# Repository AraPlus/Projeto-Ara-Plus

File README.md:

# Projeto-Ara-Plus
Repositório de projeto de um AMBU automatizado desenvolvido por estudantes, pesquisadores e professores da Universidade Federal do ABC (UFABC) para substituir um ventilador pulmonar de forma emergencial nos casos de COVID-19. Este é um trabalho em desenvolvimento, e ainda não está apto para casos clínicos. Futuras atualizações devem ser lançadas em breve.

## Origem do Nome
O nome "Ara" vem do Tupi-Guarani e significa "ar". Portanto o nome Ara-Plus reune uma palava genuinamente brasileira com uma palavra do inglês reconhecida em todo o mundo, significando literalmente "mais ar".

## Descrição geral do sistema

### Requisitos

Conforme destacado pela AMIB – [Associação de Medicina Intensiva Brasileira]() – em sua nota técnica ["Nota técnica sobre características de aparelhos ventiladores artificiais no suporte ao paciente com COVID-19"](http://www.amib.org.br/fileadmin/user_upload/amib/2020/abril/26/Nota_te__cnica_sobre_caracteri__sticas_de_aparelhos_ventiladores_artificiais_no_suporte_ao_paciente_com_COVID-19.pdf) de 26 de abril de 2020 e que atualmente (29/05/2020) subsidia o [PROJETO DE LEI N° 2294, DE 2020, em tramitação no senado,](https://www25.senado.leg.br/web/atividade/materias/-/materia/142132): "No atual cenário de pandemia por COVID-19, diante de uma situação de exceção decorrente do grande número de pacientes com necessidade de ventilação mecânica, listamos abaixo as especificações MÍNIMAS que um ventilador mecânico deve apresentar para ventilar pacientes com COVID-19, em qualquer unidade (pronto socorro, UTI ou outras unidades). Essas características devem estar presentes, independentemente de o equipamento ser ventilador de transporte ou não, ser novo ou reformado:
1. MODOS VCV e/ou PCV;
2. CONTROLE DE DELTA DE PRESSÃO (SOBRE A PEEP) NO MODO PCV (DE 5 A 30 cmH2O) E CONTROLE DE VOLUME CORRENTE INSPIRADO NO MODO VCV (de 50 A 700 ML);
3. CONTROLE DE FiO2 (21 a 100%);
4. PEEP (0 ATE 20 cm H2O);
5. CONTROLE DE TEMPO INSPIRATÓRIO (NO MODO PCV) EM SEGUNDOS (0,3 - 2,0 S) E FLUXO INSPIRATÓRIO (NO MODO VCV) - ATÉ 70L/MIN;
6. CONTROLE DE FREQUÊNCIA RESPIRATÓRIA - 8 a 40 RPM;
7. MEDIDA DE PRESSÃO DE VIAS AÉREAS (MANÔMETRO ANALÓGICO OU DIGITAL);
8. MEDIDA DE VOLUME CORRENTE EXPIRADO SEMPRE QUE POSSÍVEL;
9. ALARME DE PRESSÃO MÁXIMA EM VIAS ÁEREAS, VAZAMENTO E QUEDA DE REDE DE GASES;
10. POSSIBILIDADE DE ANEXAR FILTRO TIPO HEPA DE ALTA CAPACIDADE (N99 OU N100) NO RAMO EXPIRATÓRIO;
11. SE POSSÍVEL, POSSUIR BATERIA COM PELO MENOS 2 HORAS DE CAPACIDADE."

## Lista de Material
Descrição de todas os materiais e peças usados no Ara Plus separados por categorias:

### Partes Eletrônicas

**Diagrama elétrico do acionamento**

**Lista de materiais do acionamento**
 | Referência | Quantidade | Especificação | 
 | --------------- | --------------- | --------------- | 
 | A1 | 1 | Arduino Nano v3.x | 
 | BT1, BT2 | 2 | Bateria 12V/ 7Ah | 
 | BZ1 | 1 | Buzzer ativo 5V | 
 | C1, C4, C5 | 3 | Capacitor 0.33uF | 
 | C2, C6 | 2 | Capacitor 0.1uF | 
 | C3, C7 | 2 | Capacitor 220u
 | D1, D2, D3, D4, D5, D6, D7 | 7 | Diodo 1N4007 | 
 | M1 | 1 | Motor DC | 
 | Q1 | 1 | Transistor BC337 | 
 | RV1 | 1 | Trimpot 10K | 
 | RV2 | 1 | Potenciômetro 10K | 
 | R1, R2, R3, R4, R5, R6, R7 | 7 | Resistor 1K | 
 | S1, S2 | 2 | Sensor Indutivo NPN 12mm | 
 | SW1, SW2 | 2 | Acionador Push Buttom | 
 | U1 | 1 | Display alfanumérico 4 x 20 NHD-0420H1Z | 
 | U2, U3, U4 | 3 | Optoacoplador PC817 | 
 | U5 | 1 | Módulo Ponte H - L298N | 
 | U6, U7 | 2 | Regulador L7805 | 
 | U8 | 1 | Regulador L7812 | 
 | +24V | 1 | Fonte 24V - 5A |

### Partes Mecânicas

## Desenhos de Fabricação / Arquivos de CAD
As informações sobre os desenhos de fabricação das partes mecânicas do AraPlus encontram-se [aqui](desenhos/DESENHOS.md)

### Partes médicas

Propostas em estudo do circuito pneumático:

**Tipo 1 - Com válvula VUP**

**Tipo 2 - Com Diverter e a válvula VAP tampada de um lado**

**Tipo 3 - Com a hipótese do *Diverter* para encaixe na VAP**

## Fotos

Acionamento Mecânico

 ## Descrição dos Testes Funcionais de Bancada (in vitro)
 
**1) Levantamento da Relação PEEP x Pressão Expiratória Máxima (Vál. VAP) x Freq. Respiratória x Volume Inspirado**

**2) Levantamento da freqüência de operação, e relações Ti:Te possíveis**

Avaliar desempenho dinâmico do motor e capacidade de controle de velocidade para ajuste dos tempos.

**3) Levantamento da Relação de FIO2 e Fluxo de Oxigênio (Fluxímetro de parede)**

Referência:
GODOY, Armando Carlos Franco de; VIEIRA, Ronan José. Comparação da FiO2 fornecida por sete modelos de sistema balão-máscara auto-inflável. Rev. Bras. Anestesiol.,  Campinas ,  v. 59, n. 1, p. 21-27,  Feb.  2009 .   Available from <[http://www.scielo.br/scielo.php?script=sci_arttext&pid=S0034-70942009000100004&lng=en&nrm=iso]>. access on  22  June  2020.  [https://doi.org/10.1590/S0034-70942009000100004].

**4) Levantamento da relação de tempos determinadas mecanicamente e pelas curvas de pressão pneumática**

Averiguar para diversas condições se os tempos Ti e Te medidos pelos sensores posicionados no eixo do motor corresponde aos tempos de Ti e Te medidos pela curva de pressão/ fluxo pneumático.

**5) Calibração Estática do Sensor de Pressão**

Levantar curva de pressão medida pelo sensor MPS20N0040d comparando com uma medição de pressão estática (com manômetro U ou manômetro analógico)

**6) Calibração Dinâmica (valores simulados)**

Comparação das curvas de pressão e volume obtidas com um sensor de reverência (Analisador de Gases Fluke VT650) com as curvas de pressão obtidas com o simulador https://girardi.blumenau.ufsc.br/sdvm/, para os mesmos parâmetros ventilatórios.

**7) Calibração Dinâmica (valores experimentais)**

Comparação das curvas de pressão com um sensor de reverência, com as curvas de pressão efetivamente medidas com o sensor MPS20N0040d. Obs: o analisador  Fluke aparentemente só exporta com uma frequência de amostragem máxima de 1Hz, o que não dá uma boa resolução das curvas. A solução seria usar o sensor Magnamed Ventmeter que tem interface RS232.

**8) Determinação do procedimento de calibração do sensor de pressão embarcado**

Estabelecer rotina de calibração do sensor de pressão. Procedimento de manutenção.

## Cronologia do Desenvolvimento
Data dos principais marcos do desenvolvimento do Ara-Plus

- 25/07/2020: Proposta conceitual tecnológica para estimar FiO2 ([detalhes](./Titulação_FIO2/FIO2.md)) 
- 10/07/2020: Decidida alteração do tipo de motor e projeto em função dos novos requisitos para uso clínico em combate à COVID-19 e dos resultados dos testes em laboratório ([detalhes](./testes_de_bancada/Resultados_Motor_DC.md)) 
- 17/06/2020: Início dos testes do circuito médico/pneumático
- 07/06/2020: Finalizada a montagem do circuito de acionamento e controle
- 06/06/2020: Elaboração das propostas de circuito pneumático
- 03/03/2020: Correções a aprimoramento do acionador mecânico
- 01/06/2020: Submissão do projeto para [edital IEEE](https://hac.ieee.org/funding-opportunities/covid-19-projects/)
- 31/05/2020: Calibração do circuito condicionador do transdutor de pressão MPS20
- 18/05/2020: Finalizada a montagem do projeto mecânico
- 27/04/2020: Desenho mecânico do protótipo para testes
- 09/04/2019: Início do desenvolvimento do software
- 06/04/2020: Submissão de projeto para edital interno de pesquisa
- 03/04/2020: Testes do protótipo conceitual
- 23/03/2020: Publicação do projeto conceitual ([Tinkercad](https://www.tinkercad.com/things/d3R13CpPf5m ))
- 19/03/2020: Formação do grupo de desenvolvimento 
- 16/03/2020: Início da suspensão das aulas na UFABC devido à pandemia
- 11/03/2020: Declaração de pandemia de COVID-19 pela OMS

## Financiamento
Este projeto foi contemplado pela chamada Interna de Prospecção Para Apoio a Projetos e Ações de Pesquisa, Inovação, Extensão e Extensão Tecnológica para o Enfrentamento da Emergência de Saúde Pública Decorrente da COVID-19 da reitoria da UFABC.
Valor do financiamento: R$ 8.957,60

[http://www.ufabc.edu.br/images/reitoria/documentos/edital-42_2020-chamada-de-propostas-covid-19.pdf]

Esta projeto também conta com o apoio financeiro do IEEE HAC e IEEE SIGHT que apresentou um edital em resposta à pandemia da COVID-19.

[https://hac.ieee.org/funding-opportunities/covid-19-projects/]  

Maiores informações sobre editais com os respectivos projetos submetidos encontram-se [aqui](editais/EDITAIS.md).

## Lista de Compras 
Tabela com todos os itens adquiridos para o desenvolvimento deste projeto

Data da Compra  | Descrição do item | Quem comprou? | Origem do Recurso | Valor (R$)  
--------------- | ------------------|---------------|-------------------|------------
01/01/1900 | Exemplo 1 | Olavo | Do bolso | 10,00 
02/01/1900 | Exemplo 2 | Fulano | Edital UFABC | 20,00 
03/01/1900 | Exemplo 3 | Cicrano | Doação empresa XX | 0,00 

## Glossário
Aqui encontram-se os principais termos e siglas usados no desenvolvimento deste projeto juntamente com o seu significado:
- AMBU (Artificial Manual Breathing Unit) é que uma Unidade Manual de Respiração Artificial, ou Reanimador Manual [referência](https://enfermagemilustrada.com/unidade-manual-de-respiracao-artificial-ambu-reanimador-manual/)
- Filtro HEPA  = High Efficiency Particulate Air 
- Filtro HMEF
- Filtro Humidificador
- FiO2 - Fração Inspirada de Oxigênio ([molar ou em volume](https://en.wikipedia.org/wiki/Fraction_of_inspired_oxygen))
- PEEP (Positive end-expiratory pressure) Pressão Positiva ao Final da Expiração [referência](https://en.wikipedia.org/wiki/Positive_end-expiratory_pressure)
- Válvula VAP (?)
- Válvula VUP
- PCV = Pressão Controlada Ciclado a Tempo;
- VCV = Volume Controlado ou Ciclado a Volume;
- PSV = Ventilação com Pressão de Suporte HEPA
- FiO2 = Fração Inspirada de Oxigênio,

## Equipe
- [Olavo Luppi Silva](http://ebm.ufabc.edu.br/docentes/olavo-luppi/) - Professor Adjunto - Eng. Biomédica/UFABC
- [Erick Dario León Bueno de Camargo](http://ebm.ufabc.edu.br/docentes/erickleon/) - Professor Adjunto - Eng. Biomédica/UFABC
- [Harki Tanaka](http://ebm.ufabc.edu.br/docentes/harki-tanaka/) - Professor Adjunto - Eng. Biomédica/UFABC
- Hermann Windisch Neto - Aluno de doutorado no programa de [Biotecnociência/UFABC](http://propg.ufabc.edu.br/biotecnociencia/)
- Victor Allisson da Silva - Aluno da graduação da Engenharia Biomédica/UFABC
- Danilo Luna Campos - Aluno da graduação da Engenharia Biomédica
- Paulo Rodrigues - Aluno especial de mestrado no [PPGEBM](http://ebm.ufabc.edu.br/pos-graduacao/ppgebm/)
- Ana Tércia Lacerda de Araújo - Aluna de graduação do BC&T
- Ivan Correia Lima Coqueiro - Aluno de graduação do BC&T
- Jaqueline Badanai - Aluna de mestrado da [PPGEBM](http://ebm.ufabc.edu.br/pos-graduacao/ppgebm/)
- Danilo Buchdid - Colaborador externo
- Roberto Asano Junior - Pesquisador Pós-Doc - [Energia/UFABC](http://pgene.ufabc.edu.br)
- Edson Rodrigues - Aluno de mestrado no [PPGEBM](http://ebm.ufabc.edu.br/pos-graduacao/ppgebm/)
- [Patrícia Teixeira Leite Asano](http://cecs.ufabc.edu.br/index.php/docentes/contatos/23-docentes/143-patricia-teixeira-leite-asano.html) - Professor Associado - Eng. Energia/UFABC

## Parceiros
 - FMABC: testes clínicos
 - Prefer: usinagem 
 - Ventisilva: manufatura
  
## Agradecimentos
 - Dcryl Design em Acrílico (Campinas)
 - IEEE R9 Jt. Chapter Energy Industry Connections
 - Instituto Mauá de Tecnologia
 - Rotary-International

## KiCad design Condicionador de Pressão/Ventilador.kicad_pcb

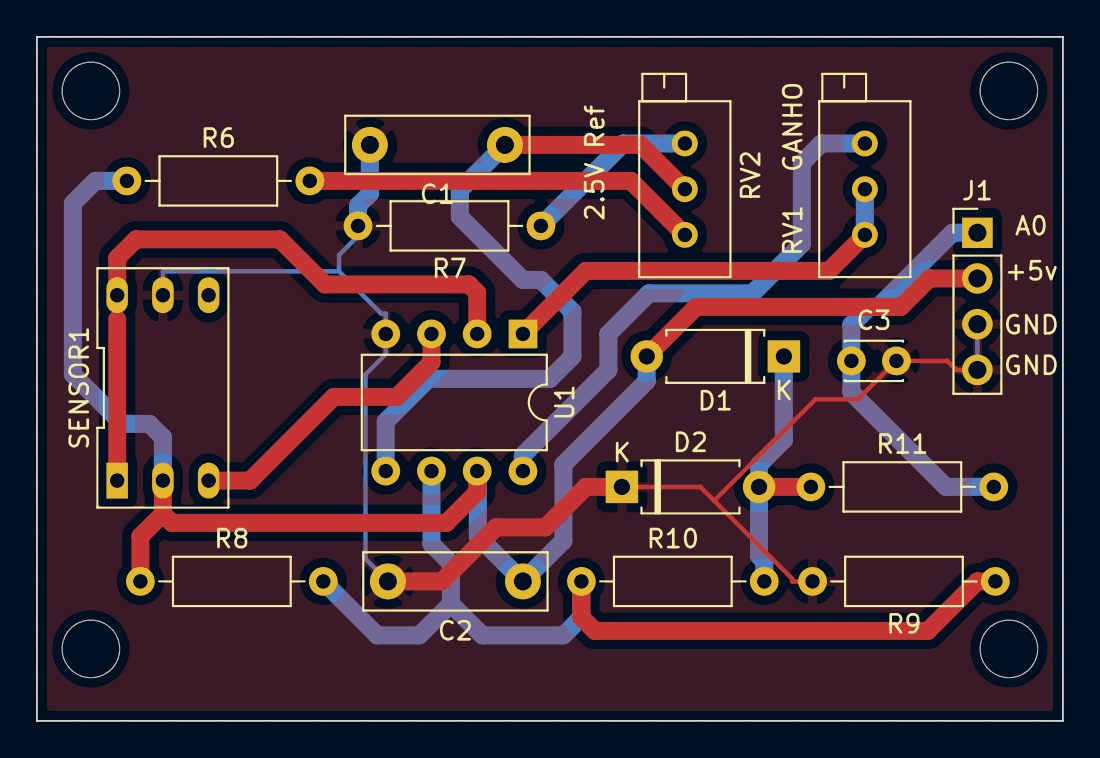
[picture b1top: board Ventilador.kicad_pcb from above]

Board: 2 copper layers, 57.0 x 38.0 mm, 16 parts (0 on the bottom side), 12 nets.

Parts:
C1, C2: 100nF; C_Rect_L10.0mm_W3.0mm_P7.50mm_MKS4
C3: 200pF; C_Disc_D3.0mm_W2.0mm_P2.50mm
D1, D2: DIODE; D_A-405_P7.62mm_Horizontal
J1: Conn_01x04_Male; PinHeader_1x04_P2.54mm_Vertical
R6, R7: 3,3k; R_Axial_DIN0207_L6.3mm_D2.5mm_P10.16mm_Horizontal
R8, R9: 10k; R_Axial_DIN0207_L6.3mm_D2.5mm_P10.16mm_Horizontal
R10: 100R; R_Axial_DIN0207_L6.3mm_D2.5mm_P10.16mm_Horizontal
R11: 6,8k; R_Axial_DIN0207_L6.3mm_D2.5mm_P10.16mm_Horizontal
RV1: 1k; Potentiometer_Bourns_3296X_Horizontal
RV2: 2k; Potentiometer_Bourns_3296X_Horizontal
SENSOR1: MPS20N0040d-S; DIP-6_405_ELL
U1: INA128; DIP-8_W7.62mm

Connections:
+5V: C2.1, D1.2, J1.2, R6.1, R8.1, SENSOR1.2, U1.7
A0: C3.1, J1.1, R11.2
GND: C1.2, C2.2, C3.2, D2.1, J1.3, J1.4, R7.2, R9.2, SENSOR1.5, U1.4
unnamed: C1.1, RV2.2, U1.5
unnamed: D1.1, D2.2, R10.2, R11.1
unnamed: R6.2, RV2.1
unnamed: R7.1, RV2.3
unnamed: R8.2, R9.1, R10.1, U1.6
unnamed: RV1.1, RV1.2, U1.1
unnamed: RV1.3, U1.8
unnamed: SENSOR1.1, SENSOR1.6, U1.2
unnamed: SENSOR1.3, U1.3

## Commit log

2020-04-11 Create AraPlus
2020-04-23 3D Printed Pieces
2020-05-18 Informações iniciais do README.md
2020-05-22 Lista de compras, materiais e glossário
    Criação dos campos lista de compras, lista de materiais e glossário para ser preencido posteriormente
2020-05-27 Adição de pasta com desenhos em pdf e dwg. Adição de pasta com os editais UFABC e IEEE e do projeto submetido para o edital UFABC.
2020-05-27 Criação da pagina DESENHOS.md para dar detalhes sobre os desenhos de fabricação das partes mecânicas.
2020-05-27 Links para pastas desenhos e pasta editais.
    Links para pastas desenhos e pasta editais. E ainda modificações em hiperlinks da Equipe e mais informações do glossário
2020-05-27 Hyperlinks editais UFABC e IEEE
2020-05-28 Correção ortográfica.
2020-06-07 Propostas circuito pneumatico
    Propostas circuito pneumatico e atualização da cronologia com edital IEEE e
2020-06-07 Imagens das propostas do circuito pneumatico
2020-06-16 Atualização de Repositório
2020-06-19 Projeto IEEE submetido
    Documento contém apenas a transcrição do formulário online que foi submetido
2020-06-19 Atualização status projeto IEEE
2020-06-19 Projeto submetido para edital IEEE
    O arquivo é uma transcrição do texto preenchido no formulário online.
2020-06-19 Correção no link
2020-06-21 Testes Funcionais de Bancada
    Criação da seção "Descrição dos Testes Funcionais de Bancada (in vitro)"
2020-06-22 Projeto-Ara-Plus
2020-06-22 Atualização do Projeto em CAD
2020-06-26 Criação de pasta com descrição de testes em bancada
2020-06-27 Complementação de info sobre experimento apos conversa com Roberto Assano
2020-06-27 Eliminei ###Resultados para melhor clareza
2020-06-27 Update TESTES_DE_BANCADA.md
    Retomados os itens 2 e 6 que estavam no README e foram perdidos na criação desta página
2020-06-28 Correção na descrição do projeto AraPlus
2020-06-28 Criando arquivo dos testes mas ainda sem dados
2020-07-26 Rename Titulação FIO2/FIO2.md to Titulação_FIO2/FIO2.md
